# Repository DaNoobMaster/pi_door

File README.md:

#Pi_Door
This project is a smart door lock created using a raspberry pi zero 2w. This is the cheapest raspberry pi capable of running what i want this project needs.
The door is capable of Face ID, Palm vein recognition, fingerprint and has a 4x4 keypad entry as well. QR codes can be generated for one time use to open the door as well.
It uses high-end secure biometric components in order to keep it reliable and safe. There is a live camera feed as well that would be transmitted from the camera to the local raspberry pi server.

The aim of this project is to make entering my house quicker and more reliable. Due to the fact that its mostly digital, it is less susceptible to intruder attacks and can help catch intruders if an attack does occur. The live camera feed is also helpful in checking who is at your at door. I belive this project would use my skills to the most. Its mechanical and software aspect is perfect for me to improve my skills and learn how to work with such types of hardware.

The 4x3 keypad can be used to enter in a pincode.
The pincode can be set to be however long.
Pressing # enters the code while * resets it. If no user input is present for 10 seconds, the code entry cache resets. If the door unlocks using other means, the code entry cache resets.

### Complete Hardware Wiring

| Subsystem | Device Pin / Signal | Connected To | Raspberry Pi Pin | GPIO / Voltage | Notes |
|----------|---------------------|--------------|------------------|----------------|-------|
| **AI Camera (Face / Palm)** | VCC | Pi 5V | Pin 4 | 5V | Camera power |
| AI Camera | GND | Pi GND | Pin 6 | GND | Common ground |
| AI Camera | UART_TX | Pi RX | Pin 10 | GPIO15 (RXD) | Camera → Pi |
| AI Camera | UART_RX | Pi TX | Pin 8 | GPIO14 (TXD) | Pi → Camera |
| **Fingerprint Sensor (via CP2102)** | VIN | CP2102 3V3 | — | 3.3V | Sensor power |
| Fingerprint | GND | CP2102 GND | — | GND | Common ground |
| Fingerprint | RX | CP2102 TXD | — | UART TX |
| Fingerprint | TX | CP2102 RXI | — | UART RX |
| Fingerprint | RST | CP2102 DTR | — | Reset |
| CP2102 | USB | Raspberry Pi | USB | — | USB-UART |
| **3×4 Keypad** | K1 (Row 1) | Pi GPIO | Pin 29 | GPIO5 | Output |
| Keypad | K2 (Row 2) | Pi GPIO | Pin 31 | GPIO6 | Output |
| Keypad | K3 (Row 3) | Pi GPIO | Pin 33 | GPIO13 | Output |
| Keypad | K4 (Row 4) | Pi GPIO | Pin 35 | GPIO19 | Output |
| Keypad | K5 (Col 1) | Pi GPIO | Pin 37 | GPIO26 | Input (PU) |
| Keypad | K6 (Col 2) | Pi GPIO | Pin 38 | GPIO20 | Input (PU) |
| Keypad | K7 (Col 3) | Pi GPIO | Pin 40 | GPIO21 | Input (PU) |
| Keypad | K8 | — | — | NC | Not connected |
| Keypad | K9 | — | — | NC | Not connected |
| Relay | Relay VCC | Pi 5V | Pin 4 | 5V | Coil power |
| Relay | Relay GND | Pi GND | Pin 6 | GND | Ground |
| **Transistor (BC107)** | Base | Pi GPIO (via resistor) | Pin 16 | GPIO23 | Drives relay |
| Transistor | Collector | 5V | — | 5V | From voltage convertor |
| Transistor | Emitter | Relay Coil | — | — | Reference |
| **Solenoid Lock** | + | External Supply | — | +7.5V | Lock power |
| Solenoid | − | Relay NO Contact | — | Switched | Controlled by relay |

### Authentication Accuracy & Error Rates

| Input Method | False Acceptance Rate (FAR) | False Rejection Rate (FRR) | Notes |
|-------------|-----------------------------|-----------------------------|-------|
| Fingerprint (Capacitive) | ~0.001% – 0.01% | ~1% – 3% | High accuracy, may fail with wet or damaged fingers |
| Face Recognition (Offline AI) | ~0.1% – 1% | ~1% – 5% | Affected by lighting, pose, and occlusion |
| Palm Recognition (Offline AI) | ~0.01% – 0.1% | ~0.5% – 2% | Very stable, less affected by lighting |
| Keypad PIN (4-digit) | 0% (if secret) | User-dependent | Security depends on PIN secrecy and length |

BOM

| S.No | Component | Purpose | Estimated Cost (₹) |
|-----:|-----------|---------|-------------------:|
| 1 | Solenoid (Door Lock) | Physically locks/unlocks the door | 800 |
| 2 | Face ID & Palm Vein Sensor | Primary biometric authentication | 5636 |
| 3 | Fingerprint Sensor | Secondary authentication | 2,042.00 |
| 4 | Raspberry Pi Zero 2 W | Main controller & processing unit | 1,587.10 |
| 5 | 18650 Battery | Portable power source | 205.32 |
| 6 | Battery Charger Module | Charging the 18650 battery | 14.00 |
| 7 | Battery Holder | Secure battery mounting | 46.00 |
| 8 | UART Converter (CP2102) | Additional UART interface for fingerprint sensor | 300.00 |
| 9 | USB to Micro-USB Cable | Power & USB connection | 54.00 |
| 10 | Barrel Jack Connector | External power input | 23.00 |
| 11 | 4×3 Keypad | Manual PIN-based fallback access | 188.00 |
| 12 | BC107 Transistor | Solenoid driver / switching | 19.00 |
| 13 | 3D Printed Parts | Enclosure & mounting brackets | — |
| 14 | Acrylic Sheet | Structural housing panels | 75.00 |
| 15 | SRD-05VDC-SL-A Relay | Solenoid isolation & control | 79.00 |
| 16 | XL6009 | Boost converter | 50.00 |
| 17 | LM2596 | Buck converter | 44.00 |
| 17 | PCB | - | 222 |
| **—** | **Total Estimated Cost** |  | **11,744.32** |

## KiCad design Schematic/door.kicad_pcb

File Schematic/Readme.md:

This folder contains all PCB design related files

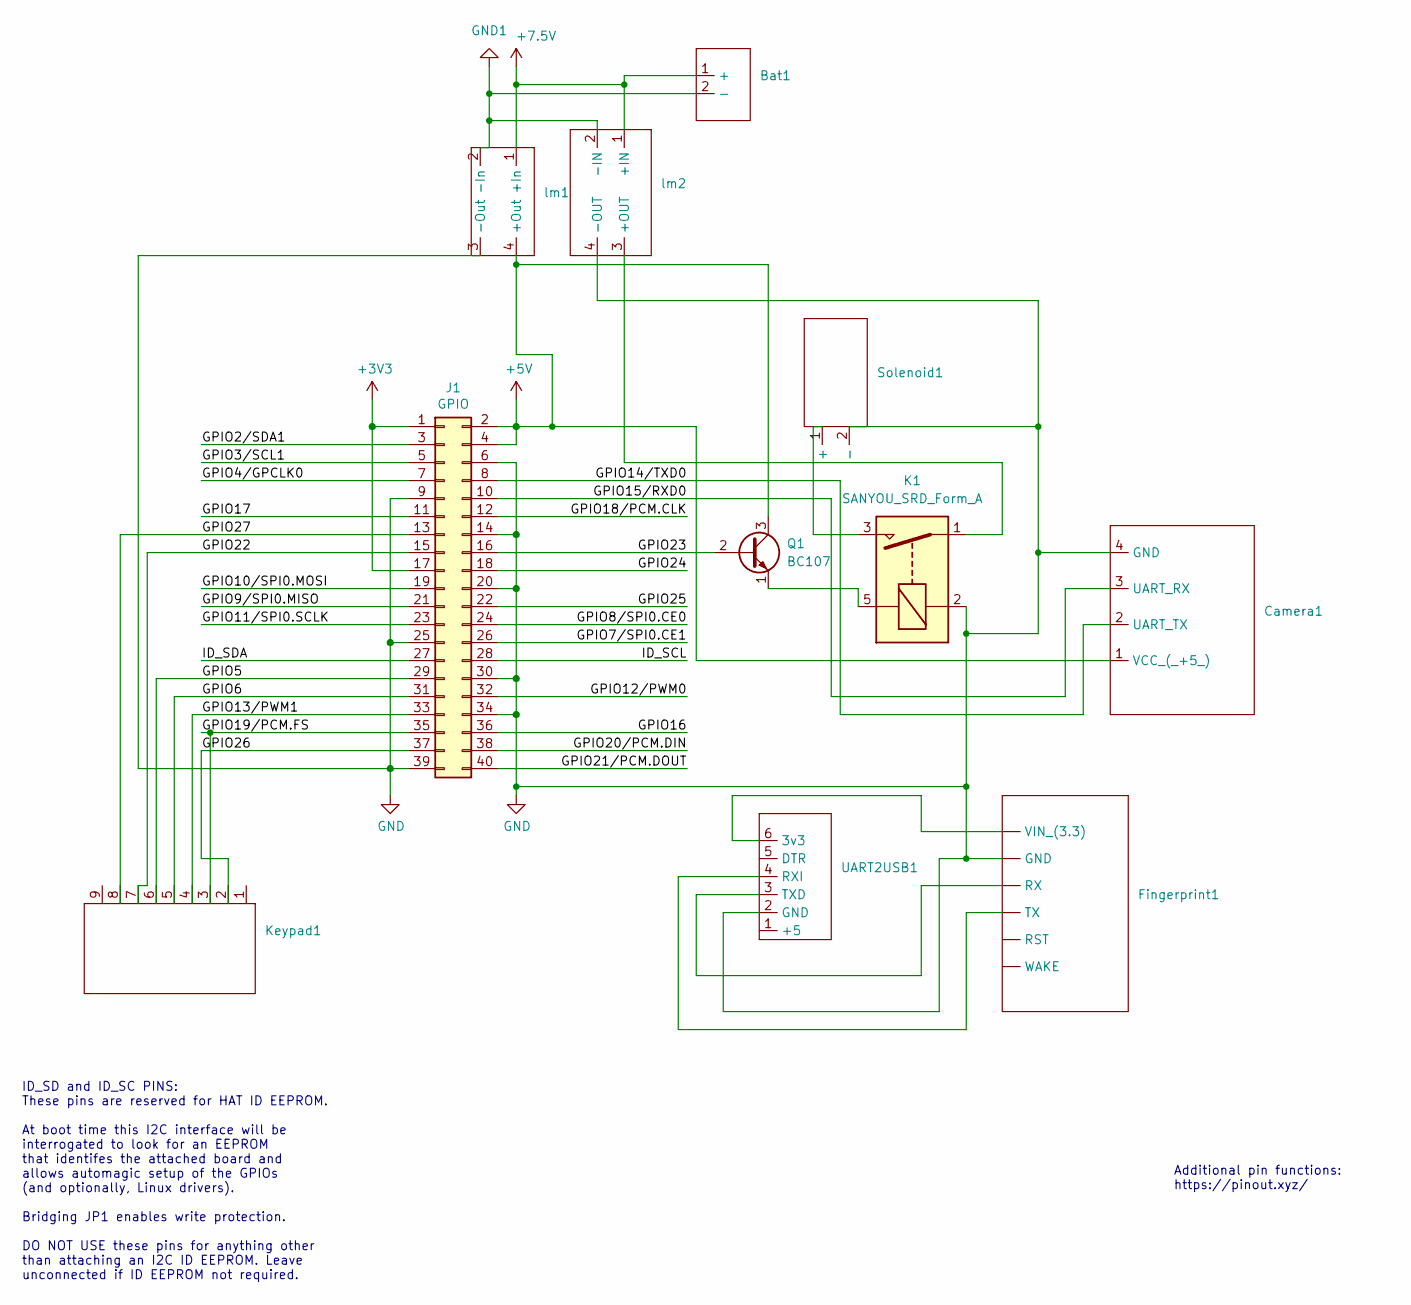
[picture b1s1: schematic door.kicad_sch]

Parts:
Bat1: Battery
Camera1: Camera
Fingerprint1: (no value)
J1: GPIO; PinSocket_2x20_P2.54mm_Vertical
K1: SANYOU_SRD_Form_A; Relay_SPST_SANYOU_SRD_Series_Form_A
Keypad1: Keypad
Q1: BC107; TO-18-3
Solenoid1: Solenoid
UART2USB1: CP2102
lm1: LM2596
lm2: XL6009_module

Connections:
+3V3: J1.1, J1.17
+5V: Camera1.1 (VCC_(_+5_)), J1.2, J1.4, Q1.3 (C), lm1.4 (+Out)
+7.5V: Bat1.1 (+), lm1.1 (+In), lm2.1 (+IN)
/GPIO2/SDA1: J1.3
/GPIO3/SCL1: J1.5
/GPIO4/GPCLK0: J1.7
/GPIO5: J1.29, Keypad1.6
/GPIO6: J1.31, Keypad1.5
/GPIO7/SPI0.CE1: J1.26
/GPIO8/SPI0.CE0: J1.24
/GPIO9/SPI0.MISO: J1.21
/GPIO10/SPI0.MOSI: J1.19
/GPIO11/SPI0.SCLK: J1.23
/GPIO12/PWM0: J1.32
/GPIO13/PWM1: J1.33, Keypad1.4
/GPIO14/TXD0: Camera1.2 (UART_TX), J1.8
/GPIO15/RXD0: Camera1.3 (UART_RX), J1.10
/GPIO16: J1.36
/GPIO17: J1.11
/GPIO18/PCM.CLK: J1.12
/GPIO19/PCM.FS: J1.35, Keypad1.3
/GPIO20/PCM.DIN: J1.38
/GPIO21/PCM.DOUT: J1.40
/GPIO22: J1.15, Keypad1.7
/GPIO23: J1.16, Q1.2 (B)
/GPIO24: J1.18
/GPIO25: J1.22
/GPIO26: J1.37, Keypad1.2
/GPIO27: J1.13, Keypad1.8
/ID_SCL: J1.28
/ID_SDA: J1.27
GND: Camera1.4 (GND), Fingerprint1., J1.6, J1.9, J1.14, J1.20, J1.25, J1.30, J1.34, J1.39, K1.2, Solenoid1.2 (-), UART2USB1.2 (GND), lm1.3 (-Out), lm2.4 (-OUT)
GND1: Bat1.2 (-), lm1.2 (-In), lm2.2 (-IN)
unnamed: Fingerprint1., UART2USB1.3 (TXD)
unnamed: Fingerprint1., UART2USB1.4 (RXI)
unnamed: Fingerprint1., UART2USB1.6 (3v3)
unnamed: K1.5, Q1.1 (E)
unnamed: K1.3, Solenoid1.1 (+)
unnamed: K1.1, lm2.3 (+OUT)

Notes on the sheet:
ID_SD and ID_SC PINS: These pins are reserved for HAT ID EEPROM. At boot time this I2C interface will be interrogated to look for an EEPROM that identifes the attached board and allows automagic setup of the GPIOs (and optionally, Linux drivers). Bridging JP1 enables write protection. DO NOT USE th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
Additional pin functions: https://pinout.xyz/

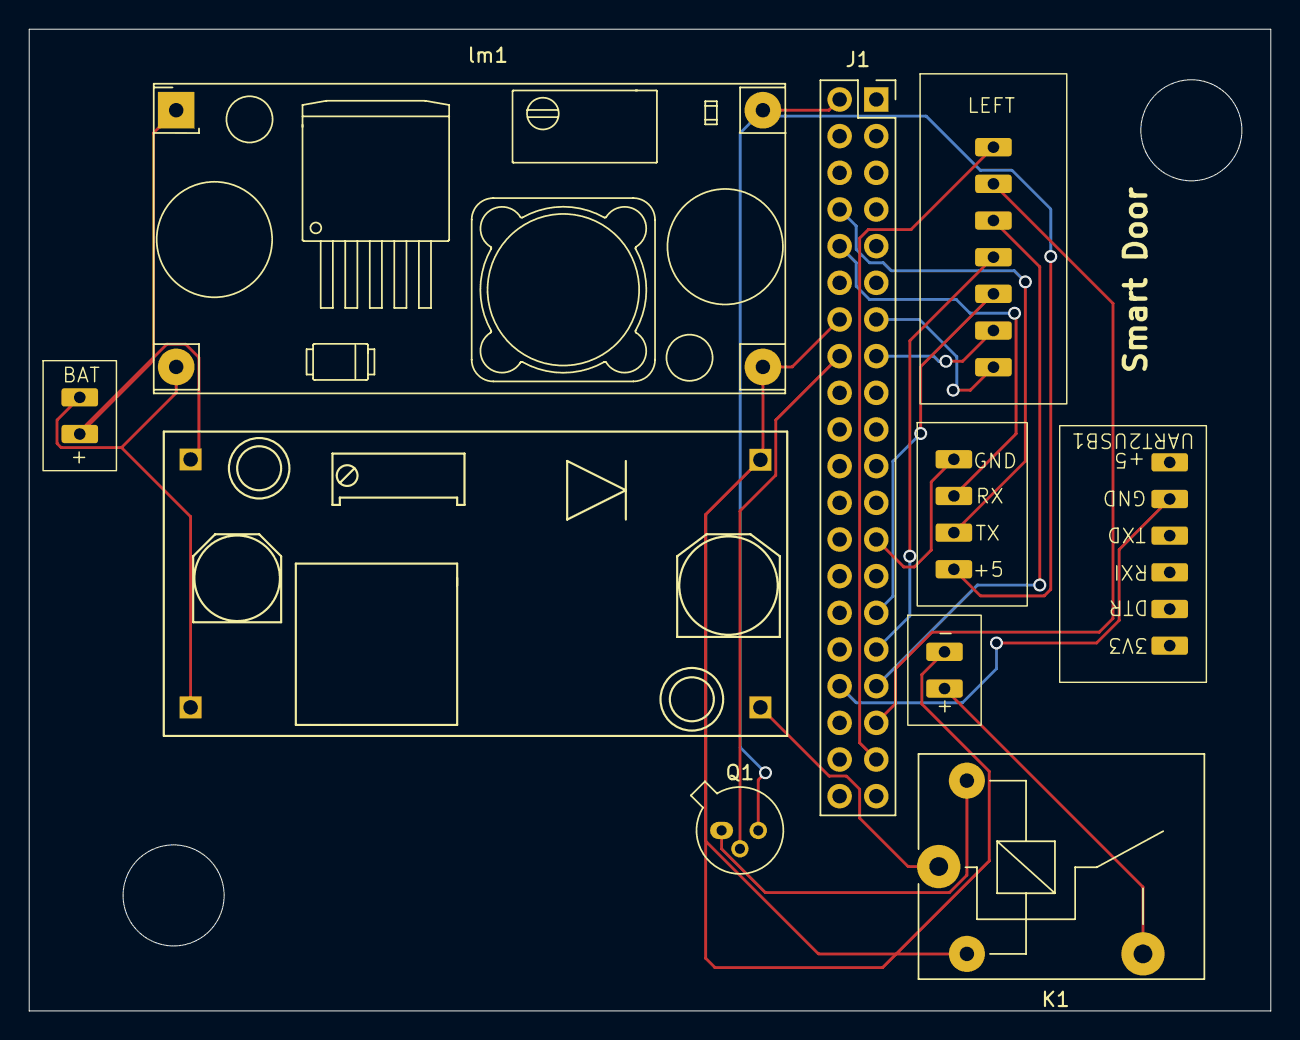
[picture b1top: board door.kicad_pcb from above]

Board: 2 copper layers, 86.0 x 68.0 mm, 10 parts (0 on the bottom side), 18 nets.

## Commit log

2026-01-20 Schematic folder
